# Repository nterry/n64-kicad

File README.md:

# n64-kicad
A set of Kicad files detailing the N64 hardware

## Special Thanks
- Acidmods.com for the various schematic pdfs
- Gman Modz for the idea of a 3x3 and for his basig images of a 3x3 layout to spingboard off
- OzOnE on the ben heck forums for finding the various deatasheets needed
- And the N64 brew discord community (especially Bigbass for his huge willingness to answer questions)

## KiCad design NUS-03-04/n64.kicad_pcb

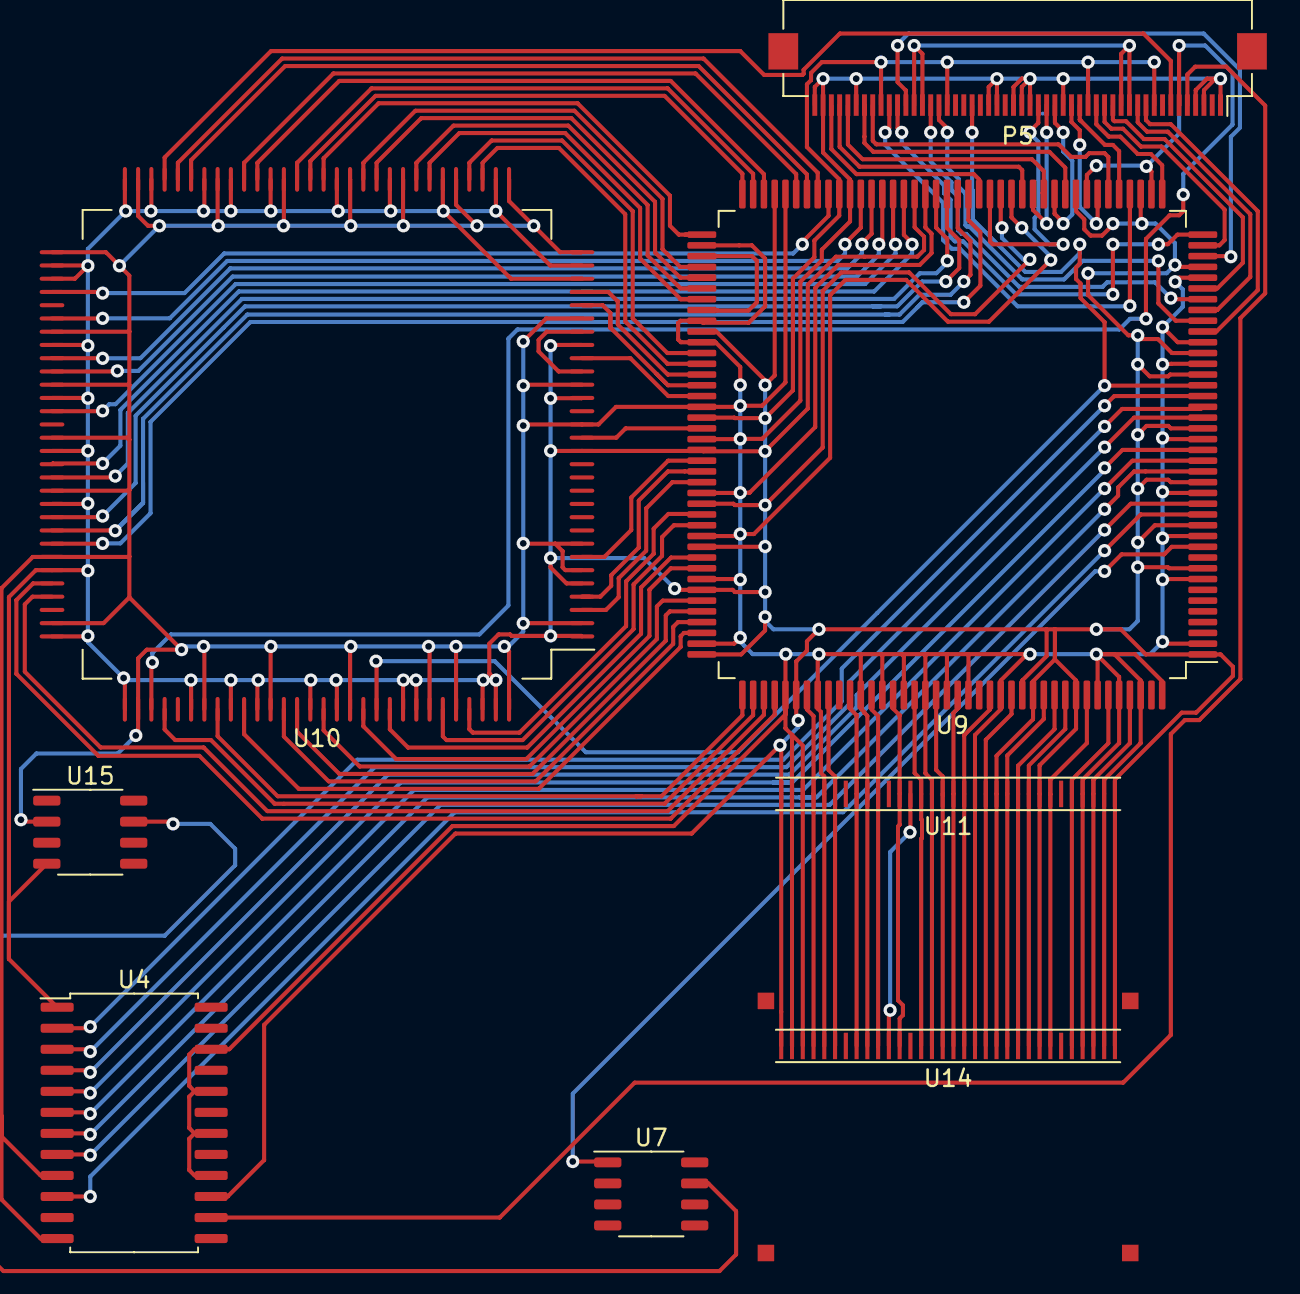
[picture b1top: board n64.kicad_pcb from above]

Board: 2 copper layers, 8 parts (0 on the bottom side), 97 nets.

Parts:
P5: CONNECTOR_CART; Hirose_FH12-50S-0.5SH_1x50-1MP_P0.50mm_Horizontal
U4: VDC-NUS; SOP-24_7.5x15.4mm_P1.27mm
U7, U15: MX8330; SOP-8_3.9x4.9mm_P1.27mm
U9: RCP-NUS; PQFP-160_28x28mm_P0.65mm
U10: CPU-NUS; PQFP-120_28x28_Pitch0.8mm
U11, U14: RDRAM-NUS

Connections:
+3V3: P5.9, P5.17, P5.34, P5.42, U4.1, U4.15, U7.4, U9.1, U9.9, U9.13, U9.17, U9.22, U9.27, U9.29, U9.37, U9.43, U9.49, U9.56, U9.64, U9.71, U9.77, U9.83, U9.88, U9.90, U9.98, U9.101, U9.106, U9.110, U9.114, U9.120, U9.126, U9.130, U9.141, U9.143, U9.147, U9.148, U9.152, U10.1, U10.5, U10.15, U10.19, U10.23, U10.28, U10.29, U10.32, U10.36, U10.40, U10.44, U10.49, U10.52, U10.54, U10.58, U10.60, U10.62, U10.63, U10.68, U10.72, U10.76, U10.80, U10.85, U10.90, U10.91, U10.96, U10.99, U10.101, U10.105, U10.107, U10.112, U10.113, U10.118, U10.119, U11.1, U11.8, U11.12, U11.16, U11.32, U14.1, U14.8, U14.12, U14.16, U14.20, U14.32, U15.4
+12V: P5.13, P5.14, P5.38, P5.39
/VREF: U9.135, U11.21, U14.21
GND: P5.1, P5.2, P5.6, P5.22, P5.23, P5.25, P5.26, P5.27, P5.31, P5.47, P5.48, P5.50, U4.9, U4.12, U4.16, U4.18, U4.20, U4.22, U7.2, U9.2, U9.8, U9.12, U9.16, U9.21, U9.28, U9.30, U9.36, U9.42, U9.48, U9.55, U9.63, U9.70, U9.76, U9.82, U9.89, U9.91, U9.97, U9.100, U9.105, U9.109, U9.113, U9.119, U9.125, U9.128, U9.132, U9.134, U9.136, U9.138, U9.140, U9.142, U9.145, U9.150, U9.154, U9.156, U9.158, U9.160, U10.2, U10.6, U10.8, U10.17, U10.20, U10.25, U10.30, U10.31, U10.35, U10.39, U10.43, U10.48, U10.53, U10.59, U10.61, U10.67, U10.71, U10.75, U10.79, U10.84, U10.89, U10.92, U10.97, U10.102, U10.108, U10.114, U10.116, U10.120, U11.2, U11.4, U11.10, U11.14, U11.18, U11.24, U11.28, U11.30, U11.31, U14.2, U14.4, U14.10, U14.14, U14.18, U14.24, U14.28, U14.30, U14.31, U15.2
unnamed: U10.10, U10.14
unnamed: U10.9, U10.13
unnamed: U7.7, U15.7
unnamed: U9.157, U11.3, U14.3
unnamed: U9.155, U11.5, U14.5
unnamed: U9.153, U11.7, U14.7
unnamed: U9.151, U11.9, U14.9
unnamed: U9.149, U11.11, U14.11
unnamed: U9.146, U11.13, U14.13
unnamed: U9.144, U11.15, U14.15
unnamed: U9.139, U11.17, U14.17
unnamed: U9.137, U11.19, U14.19
unnamed: U9.133, U11.23, U14.23
unnamed: U9.131, U11.25, U14.25
unnamed: U9.129, U11.27, U14.27
unnamed: U9.127, U11.29, U14.29
unnamed: P5.3, U9.58
unnamed: P5.4, U9.54
unnamed: P5.5, U9.52
unnamed: P5.7, U9.50
unnamed: P5.8, U9.46
unnamed: P5.10, U9.44
unnamed: P5.11, U9.40
unnamed: P5.12, U9.38
unnamed: P5.15, U9.34
unnamed: P5.16, U9.32
unnamed: P5.20, U9.26, U10.110
unnamed: P5.28, U9.57
unnamed: P5.29, U9.53
unnamed: P5.30, U9.51
unnamed: P5.32, U9.47
unnamed: P5.33, U9.45
unnamed: P5.35, U9.41
unnamed: P5.36, U9.39
unnamed: P5.37, U9.35
unnamed: P5.40, U9.33
unnamed: P5.41, U9.31
unnamed: P5.44, U10.57
unnamed: P5.45, U10.93
unnamed: P5.46, U4.14
unnamed: U7.1, U9.11
unnamed: U4.2, U9.25
unnamed: U4.3, U9.24
unnamed: U4.4, U9.23
unnamed: U4.5, U9.20
unnamed: U4.6, U9.19
unnamed: U4.7, U9.18
unnamed: U4.8, U9.15
unnamed: U4.10, U9.14
unnamed: U9.104, U10.3
unnamed: U9.103, U10.4
unnamed: U9.102, U10.7
unnamed: U9.99, U10.16
unnamed: U10.21, U10.24
unnamed: U9.96, U10.22
unnamed: U9.95, U10.26
unnamed: U9.94, U10.27
unnamed: U9.93, U10.33
unnamed: U9.92, U10.34
unnamed: U9.87, U10.37
unnamed: U9.86, U10.38
unnamed: U9.85, U10.41
unnamed: U9.84, U10.42
unnamed: U9.81, U10.45
unnamed: U9.80, U10.46
unnamed: U9.79, U10.47
unnamed: U9.78, U10.50
unnamed: U9.75, U10.51
unnamed: U9.74, U10.55
unnamed: U9.73, U10.56
unnamed: U9.72, U10.64
unnamed: U9.69, U10.66
unnamed: U9.68, U10.69
unnamed: U9.67, U10.70
unnamed: U9.66, U10.73
unnamed: U9.65, U10.77
unnamed: U9.62, U10.78
unnamed: U9.61, U10.81
unnamed: U9.60, U10.82
unnamed: U9.59, U10.83
unnamed: U9.124, U10.86
unnamed: U9.123, U10.87
unnamed: U9.122, U10.94
unnamed: U9.121, U10.98
unnamed: U9.118, U10.100
unnamed: U9.117, U10.103
unnamed: U9.116, U10.104
unnamed: U9.115, U10.106
unnamed: U9.112, U10.109
unnamed: U9.111, U10.111
unnamed: U9.108, U10.115
unnamed: U9.107, U10.117
unnamed: U11.20, U14.22

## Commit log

2021-01-30 Added initial contents for NUS 03 and 04
2021-01-30 Updated README to include credits for stuff
